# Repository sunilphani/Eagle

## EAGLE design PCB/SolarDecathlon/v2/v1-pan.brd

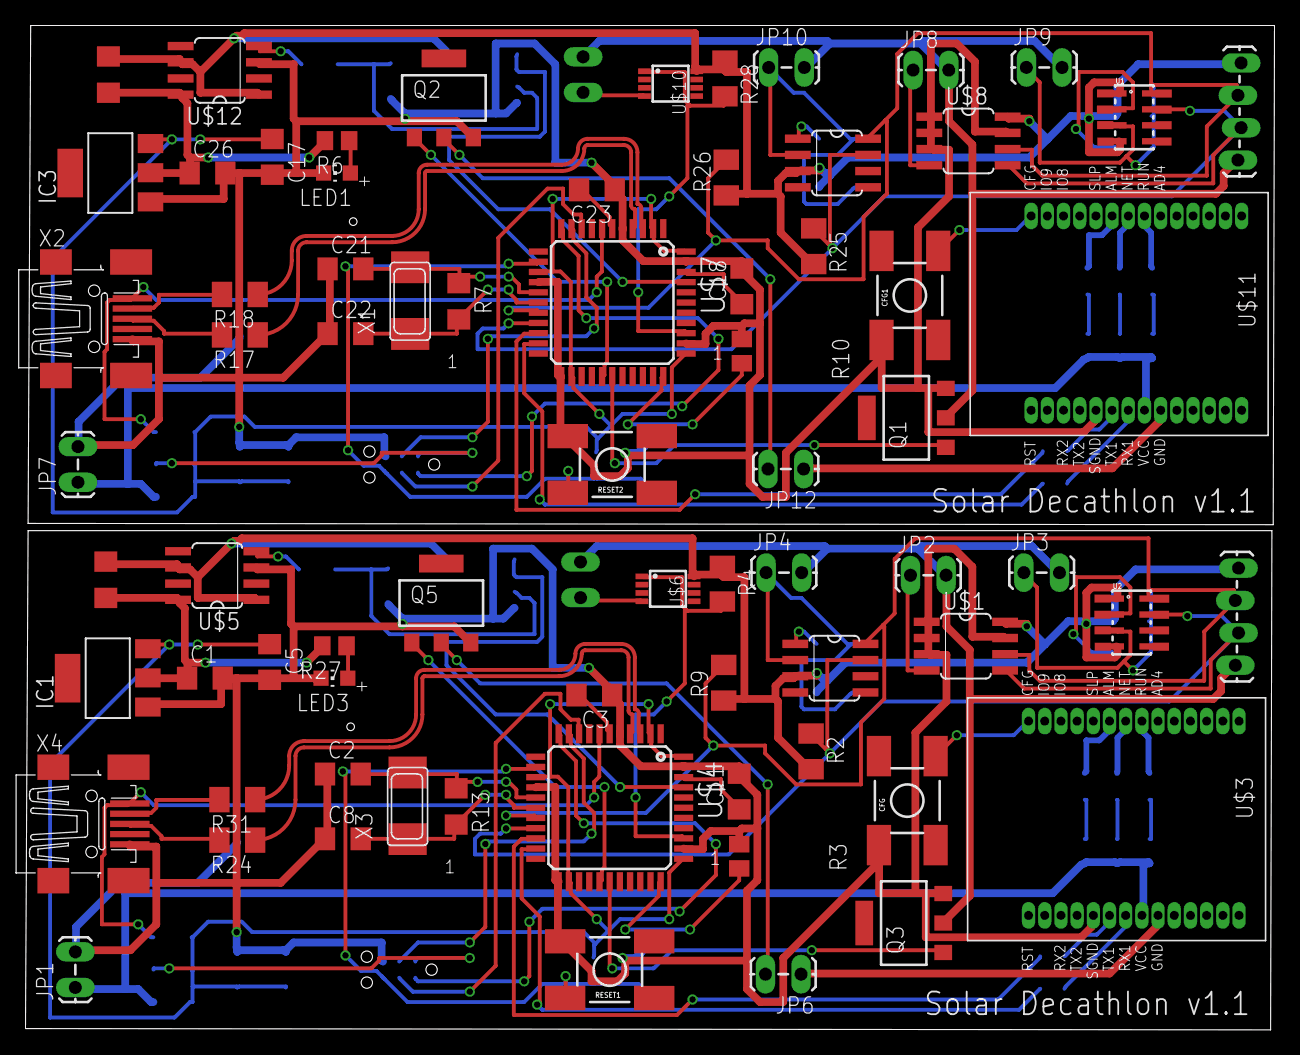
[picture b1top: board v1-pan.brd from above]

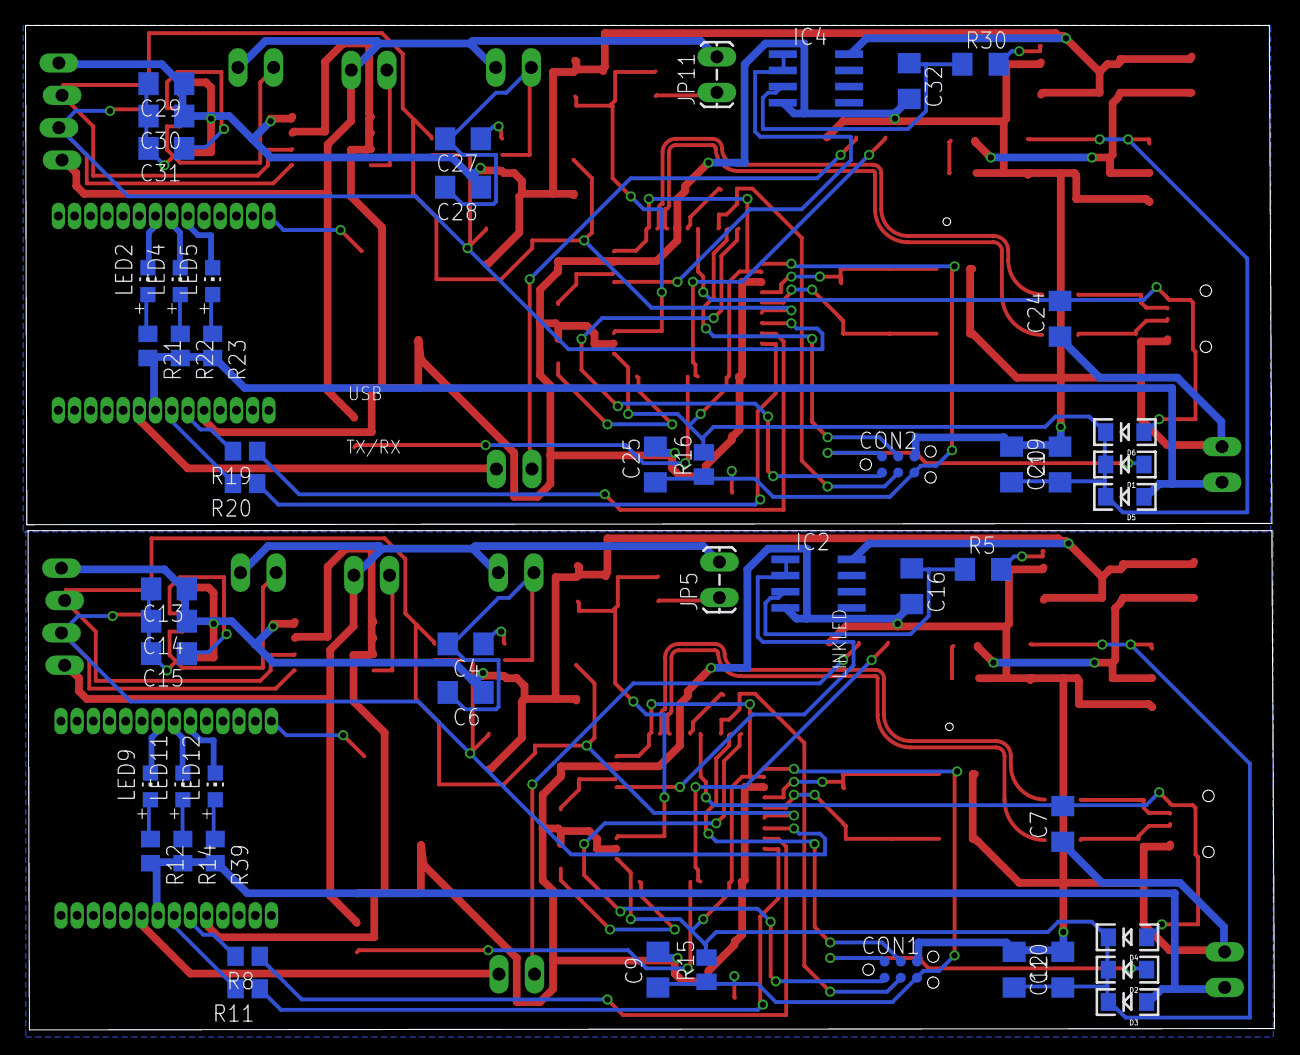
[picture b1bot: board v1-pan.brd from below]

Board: 2 copper layers, 98.0 x 78.8 mm, 124 parts (52 on the bottom side), 98 nets.

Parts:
C1, C5, C7, C10, C14, C17, C19, C24, C26, C30: 10uF; C1206
C2, C8, C21, C22: 22pF; C1206
C3, C4, C9, C11, C12, C13, C15, C18, C20, C23, C25, C27, C29, C31: 100nF; C1206
C6, C28: 220nF; C1206
C16, C32: 150nF; C1206
CFG, CFG1: Configure; TACTILE_SWITCH_SMD
CON1, CON2: SPI; TC2030-MCP-NL
D1, D2, D3, D4, D5, D6: 1N581D1206; LED-1206
IC1, IC3: REG1117; SOT223
IC2, IC4: TL072D; SO08
JP1, JP2, JP3, JP4, JP5, JP6, JP7, JP8, JP9, JP10, JP11, JP12: 1X02_LOCK_LONGPADS
JP13, JP14: 1X04_LOCK_LONGPADS
LED1, LED2, LED3, LED4, LED5, LED9, LED11, LED12: RED; CHIP-LED0805
Q1, Q2, Q3, Q5: BSP75; PG-SOT-223
R1, R29: 50m; R1206
R2, R9, R25, R26: 10k; M1206
R3, R10, R15, R16: 10k; M0805
R4, R28: 4.7k; M1206
R5, R30: 10k; R1206
R6, R8, R11, R12, R14, R19, R20, R21, R22, R23, R27, R39: 1K; R0805
R7, R13: 1M; R1206
R17, R18, R24, R31: 22; M1206
RESET1, RESET2: Reset uC; TACTILE_SWITCH_SMD
U1, U2: MPL3115A2LGA8; LGA8
U$1, U$8: M24512; SO8
U$2, U$9: CHIPCAP
U$3, U$11: SZ05-ZIGBEETHROUGHHOLE; SZ05-ZIGBEE4
U$4, U$7: ATMEGA32U4-AU; TQFP44
U$5, U$12: MAX4376F; SO8
U$6, U$10: DS1820; µSOP8
X1, X3: 16MHz; NX6035
X2, X4: MINI-USB; 32005-201

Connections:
3.3IN: C1.1, IC1.2, R1.1, R27.2, U$5.8
3.3IN1: C26.1, IC3.2, R6.2, R29.1, U$12.8
3.3V: C6.1, C13.1, C14.1, IC2.8, JP13.1, R1.2, R2.2, R4.1, R9.1, U2.1, U2.4, U$1.8, U$2.3, U$5.1, U$5.6, U$6.8
3.3V1: C28.1, C29.1, C30.1, IC4.8, JP14.1, R25.2, R26.1, R28.1, R29.2, U1.1, U1.4, U$8.8, U$9.3, U$10.8, U$12.1, U$12.6
$1: C13.2, C14.2, C15.2, JP3.1, U2.3
$2: C4.2, C6.2, JP4.1, U$2.2
$3: JP5.1, U$6.4
$4: JP8.1, U$8.4
$5: JP11.1, U$10.4
$6: C29.2, C30.2, C31.2, JP9.1, U1.3
$7: C27.2, C28.2, JP10.1, U$9.2
$12: JP2.1, U$1.4
+5V: D3.A, JP1.1, R12.2, R14.2, R39.2, U$3.VCC
+5V1: D5.A, JP7.1, R21.2, R22.2, R23.2, U$11.VCC
A0: R4.2, U$4.36, U$6.1
A5: IC2.1, IC2.2, U$4.41
A9: IC4.1, IC4.2, U$7.41
A11: R28.2, U$7.36, U$10.1
AREF: C11.1, U$4.42
AREF1: C18.1, U$7.42
D6*: Q5.1, U$4.27
D6*1: Q2.1, U$7.27
D8*: Q3.1, U$4.28
D8*1: Q1.1, U$7.28
D+USB: R24.2, X4.3
D+USB1: R17.2, X2.3
D-USB: R31.2, X4.2
D-USB1: R18.2, X2.2
GND: C1.2, C2.1, C3.1, C5.2, C7.1, C8.1, C9.2, C10.2, C11.2, C12.1, C16.2, CFG.1, CON1.GND, IC1.1, IC2.4, JP1.2, LED3.C, Q3.3, Q5.3, R3.1, RESET1.4, U$1.1, U$1.2, U$1.3, U$1.7, U$3.SND, U$4.5, U$4.15, U$4.23, U$4.35, U$4.43, U$5.3, X4.5
GND1: LED9.C, U$3.RUN
GND2: LED11.C, U$3.NET
GND3: LED12.C, U$3.ALM
GND4: C17.2, C18.2, C19.2, C20.1, C21.1, C22.1, C23.1, C24.1, C25.2, C26.2, C32.2, CFG1.1, CON2.GND, IC3.1, IC4.4, JP7.2, LED1.C, Q1.3, Q2.3, R10.1, RESET2.4, U$7.5, U$7.15, U$7.23, U$7.35, U$7.43, U$8.1, U$8.2, U$8.3, U$8.7, U$11.SND, U$12.3, X2.5
GND5: LED2.C, U$11.RUN
GND6: LED4.C, U$11.NET
GND7: LED5.C, U$11.ALM
GND_CONTROLLED: JP2.2, JP3.2, JP4.2, JP5.2, JP13.4, Q3.2
GND_CONTROLLED1: JP8.2, JP9.2, JP10.2, JP11.2, JP14.4, Q1.2
HWB: R3.2, U$4.33
HWB1: R10.2, U$7.33
ISP+5V: CON1.5V, D2.A
ISP+5V1: CON2.5V, D1.A
MISO: CON1.MISO, U$4.11
MISO1: CON2.MISO, U$7.11
MOSI: CON1.MOSI, U$4.10
MOSI1: CON2.MOSI, U$7.10
unnamed: R5.2, U$5.4
unnamed: JP6.2, Q5.2
unnamed: C16.1, IC2.3, R5.1
unnamed: C22.2, R7.2, U$7.17, X1.P$2
unnamed: LED1.A, R6.1
unnamed: C4.1, U$2.1
unnamed: C23.2, U$7.6
unnamed: JP6.1, U$3.GND
unnamed: R20.2, U$11.RX1
unnamed: R19.2, U$11.TX1
unnamed: R11.2, U$3.RX1
unnamed: LED2.A, R21.1
unnamed: C15.1, U2.2
unnamed: LED4.A, R22.1
unnamed: LED5.A, R23.1
unnamed: C3.2, U$4.6
unnamed: CFG1.4, U$11.CFG
unnamed: C27.1, U$9.1
unnamed: C31.1, U1.2
unnamed: LED3.A, R27.1
unnamed: JP12.1, U$11.GND
unnamed: JP12.2, Q2.2
unnamed: R30.2, U$12.4
unnamed: R8.2, U$3.TX1
unnamed: LED9.A, R12.1
unnamed: LED11.A, R14.1
unnamed: LED12.A, R39.1
unnamed: C32.1, IC4.3, R30.1
unnamed: CFG.4, U$3.CFG
unnamed: C8.2, R13.2, U$4.17, X3.P$2
RD_N: R31.1, U$4.3
RD_N1: R18.1, U$7.3
RD_P: R24.1, U$4.4
RD_P1: R17.1, U$7.4
RESET: C9.1, CON1.RESET, R15.1, RESET1.2, U$4.13
RESET1: C25.1, CON2.RESET, R16.1, RESET2.2, U$7.13
RX: R8.1, U$4.20
RX1: R19.1, U$7.20
SCK: CON1.SCK, U$4.9
SCK1: CON2.SCK, U$7.9
SCL: JP13.2, R9.2, U2.8, U$1.6, U$2.8, U$4.18
SCL1: JP14.2, R26.2, U1.8, U$7.18, U$8.6, U$9.8
SDA: JP13.3, R2.1, U2.7, U$1.5, U$2.7, U$4.19
SDA1: JP14.3, R25.1, U1.7, U$7.19, U$8.5, U$9.7
TX: R11.1, U$4.21
TX1: R20.1, U$7.21
VCC: C5.1, C10.1, C12.2, D2.C, D3.C, D4.C, IC1.3, R15.2, U$4.2, U$4.14, U$4.24, U$4.34, U$4.44
VCC1: C17.1, C19.1, C20.2, D1.C, D5.C, D6.C, IC3.3, R16.2, U$7.2, U$7.14, U$7.24, U$7.34, U$7.44
VUSB: C7.2, D4.A, U$4.7, X4.1
VUSB1: C24.2, D6.A, U$7.7, X2.1
XTAL1: C2.2, R13.1, U$4.16, X3.P$1
XTAL2: C21.2, R7.1, U$7.16, X1.P$1

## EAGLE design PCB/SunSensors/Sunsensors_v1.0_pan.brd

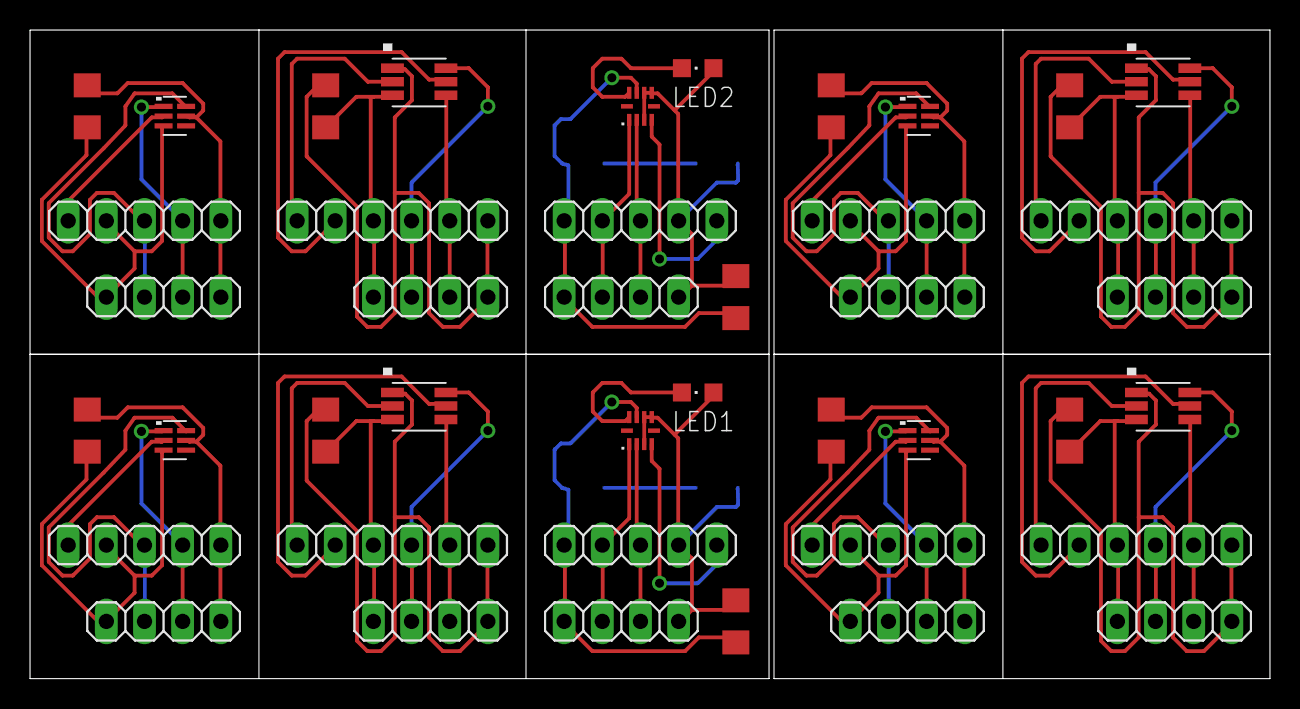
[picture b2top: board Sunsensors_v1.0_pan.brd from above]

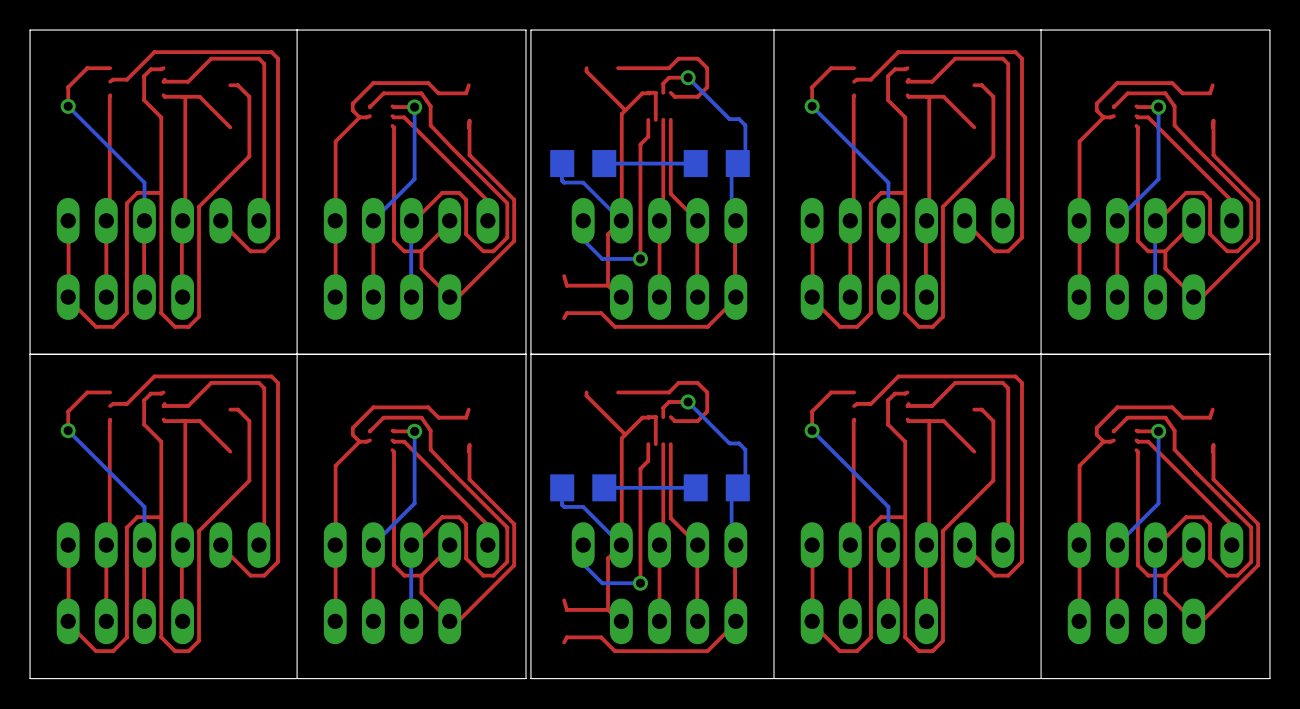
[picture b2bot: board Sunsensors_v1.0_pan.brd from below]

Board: 2 copper layers, 82.5 x 43.2 mm, 46 parts (4 on the bottom side), 46 nets.

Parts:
C1, C2, C3, C5, C6, C7, C9, C10, C11, C12: 0.1uF; C1206
C4, C8: 15uF; C1206
IC1, IC2: SI1145; QFN-10
JP1, JP3, JP5, JP7, JP9, JP11, JP13, JP15, JP17, JP19: 1X04
JP2, JP6, JP8, JP12, JP14, JP18: 1X05
JP4, JP10, JP16, JP20: 1X06
LED1, LED2: CHIPLED_0805
R1, R2: 30; C1206
U$1, U$3, U$5, U$8: TSL25911FN; ODFN6
U$2, U$4, U$6, U$9: TSL2561T; TMB-6

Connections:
ADDR1: JP4.6, U$9.P$2
ADDR2: JP10.6, U$2.P$2
ADDR3: JP16.6, U$4.P$2
ADDR4: JP20.6, U$6.P$2
GND: C3.2, C4.2, IC1.8, JP5.4, JP6.5
GND1: C2.2, JP1.4, JP2.4, U$8.P$3
GND2: C1.2, JP3.4, JP4.4, U$9.P$3
GND3: C7.2, C8.2, IC2.8, JP11.4, JP12.5
GND4: C6.2, JP7.4, JP8.4, U$1.P$3
GND5: C5.2, JP9.4, JP10.4, U$2.P$3
GND6: C10.2, JP13.4, JP14.4, U$3.P$3
GND7: C9.2, JP15.4, JP16.4, U$4.P$3
GND8: C12.2, JP17.4, JP18.4, U$5.P$3
GND9: C11.2, JP19.4, JP20.4, U$6.P$3
INT1: JP4.5, U$9.P$5
INT2: JP2.5, U$8.P$2
INT3: IC1.4, JP6.1
INT4: JP10.5, U$2.P$5
INT5: JP8.5, U$1.P$2
INT6: IC2.4, JP12.1
INT7: JP16.5, U$4.P$5
INT8: JP14.5, U$3.P$2
INT9: JP20.5, U$6.P$5
INT10: JP18.5, U$5.P$2
unnamed: C4.1, R1.1
unnamed: IC2.9, LED2.C
unnamed: IC1.9, LED1.C
unnamed: C8.1, R2.1
SCL: IC1.2, JP1.2, JP2.2, JP3.2, JP4.2, JP5.2, JP6.3, U$8.P$1, U$9.P$4
SCL1: IC2.2, JP7.2, JP8.2, JP9.2, JP10.2, JP11.2, JP12.3, U$1.P$1, U$2.P$4
SCL2: JP13.2, JP14.2, JP15.2, JP16.2, U$3.P$1, U$4.P$4
SCL3: JP17.2, JP18.2, JP19.2, JP20.2, U$5.P$1, U$6.P$4
SDA: IC1.1, JP1.3, JP2.3, JP3.3, JP4.3, JP5.3, JP6.4, U$8.P$6, U$9.P$6
SDA1: IC2.1, JP7.3, JP8.3, JP9.3, JP10.3, JP11.3, JP12.4, U$1.P$6, U$2.P$6
SDA2: JP13.3, JP14.3, JP15.3, JP16.3, U$3.P$6, U$4.P$6
SDA3: JP17.3, JP18.3, JP19.3, JP20.3, U$5.P$6, U$6.P$6
VCC: C3.1, IC1.3, IC1.6, IC1.7, JP5.1, JP6.2, LED1.A, R1.2
VCC1: C2.1, JP1.1, JP2.1, U$8.P$5
VCC2: C1.1, JP3.1, JP4.1, U$9.P$1
VCC3: C7.1, IC2.3, IC2.6, IC2.7, JP11.1, JP12.2, LED2.A, R2.2
VCC4: C6.1, JP7.1, JP8.1, U$1.P$5
VCC5: C5.1, JP9.1, JP10.1, U$2.P$1
VCC6: C10.1, JP13.1, JP14.1, U$3.P$5
VCC7: C9.1, JP15.1, JP16.1, U$4.P$1
VCC8: C12.1, JP17.1, JP18.1, U$5.P$5
VCC9: C11.1, JP19.1, JP20.1, U$6.P$1

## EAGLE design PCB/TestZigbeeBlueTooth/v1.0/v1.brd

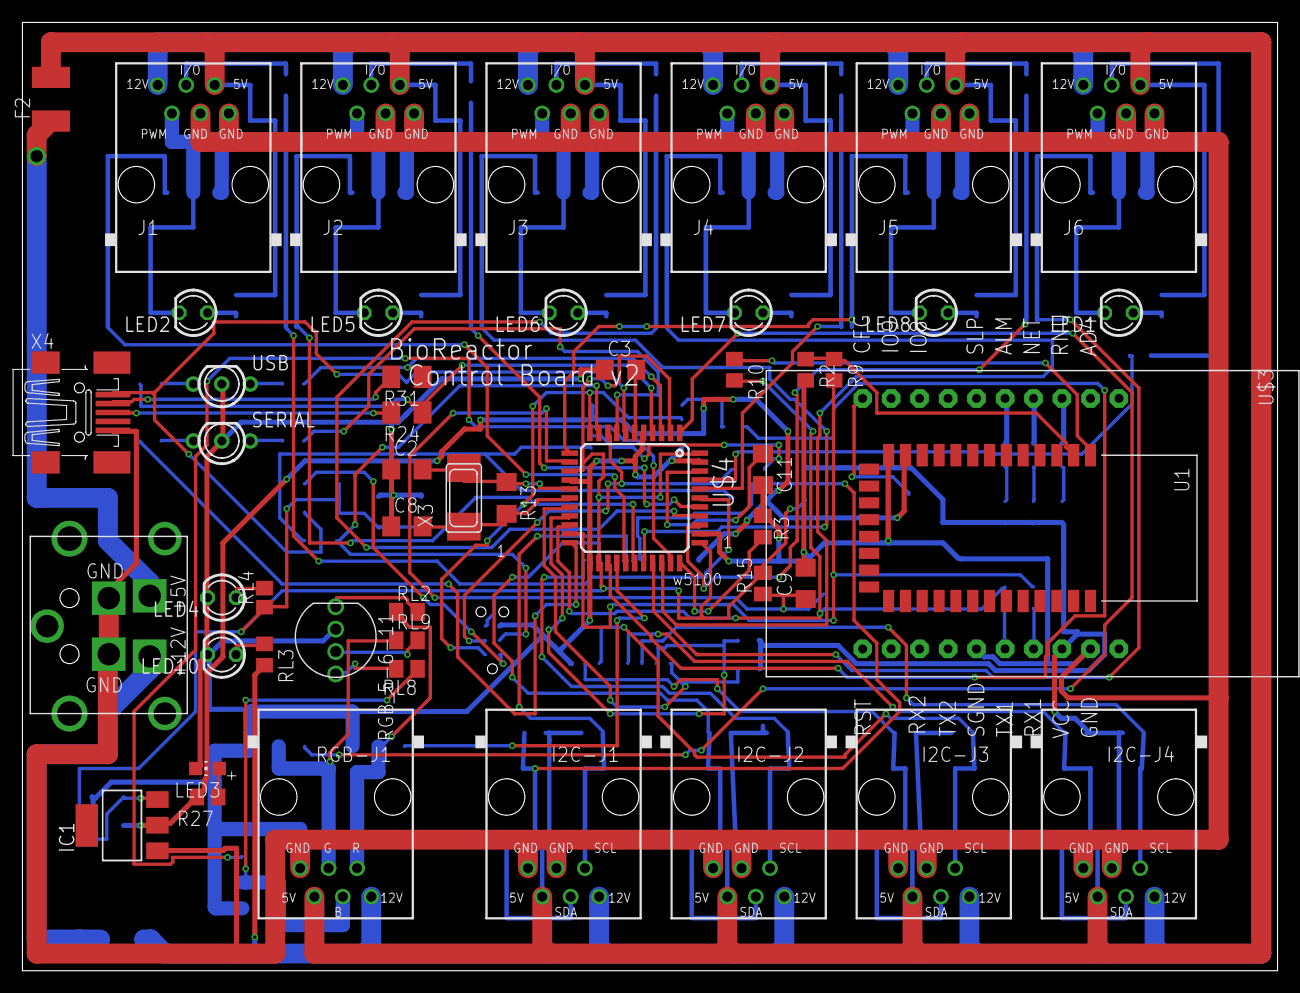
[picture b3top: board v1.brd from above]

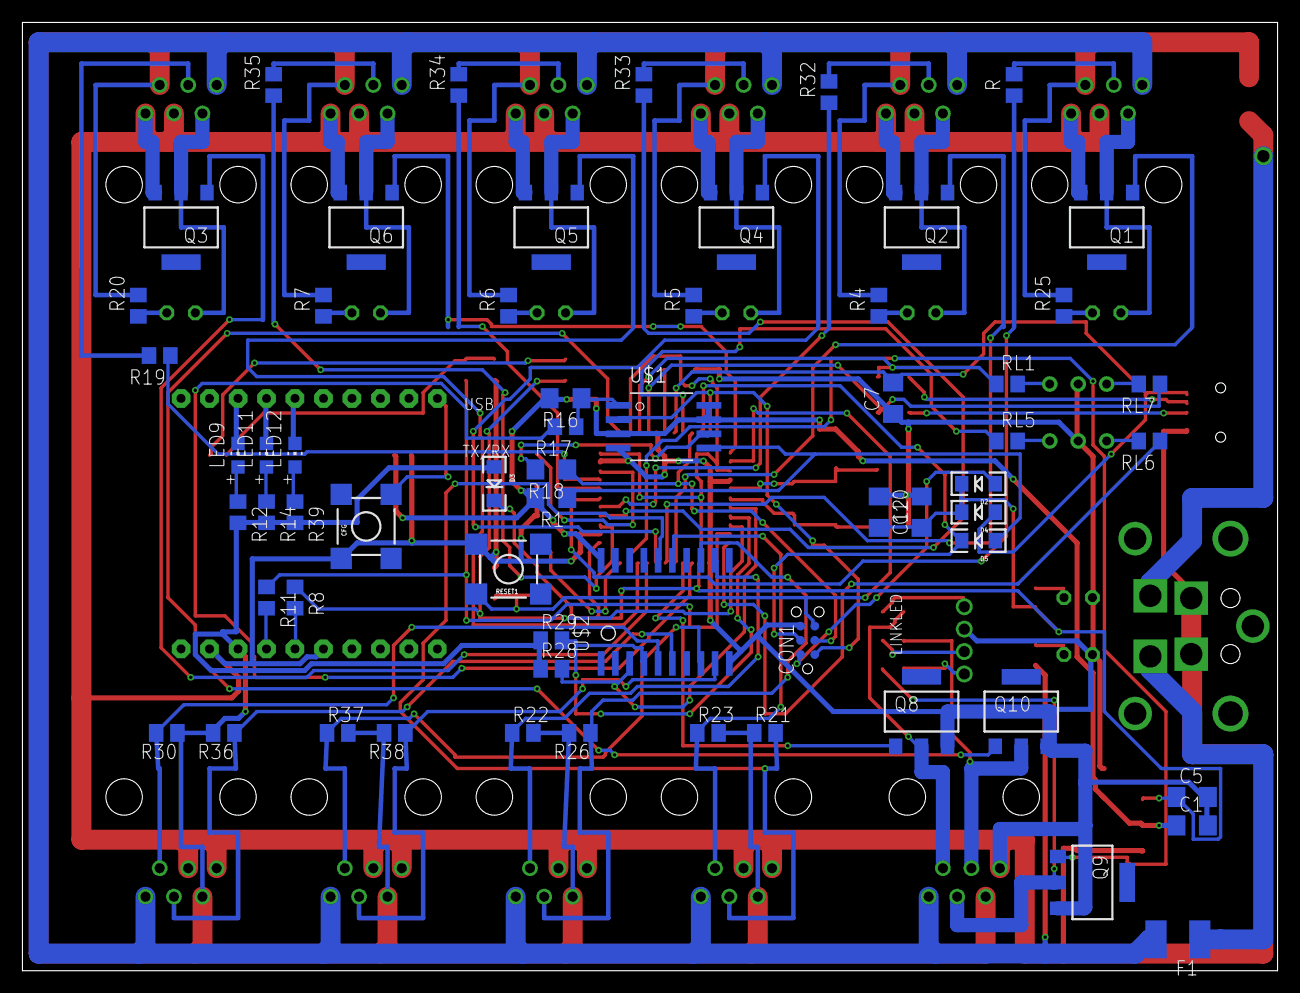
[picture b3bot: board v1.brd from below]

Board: 2 copper layers, 111.9 x 84.6 mm, 112 parts (62 on the bottom side), 97 nets.

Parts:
C1, C5, C7, C10: 10uF; C1206
C2, C8: 22pF; C1206
C3, C9, C11, C12: 100nF; C1206
CFG: Configure; TACTILE_SWITCH_SMD
CON1: SPI; TC2030-MCP-NL
D2, D3, D4, D5: 1N581D1206; LED-1206
F1, F2: 0.5A; C1812
I2C-J1, I2C-J2, I2C-J3, I2C-J4: RJ12STRAIGHT-I2C; RJ12-STRAIGHT-I2C
IC1: REG1117; SOT223
J1, J2, J3, J4, J5, J6: RJ12; RJ12-STRAIGHT
LED1, LED2, LED5, LED6, LED8: Blue; LED3MM
LED3, LED9, LED11, LED12: RED; CHIP-LED0805
LED4, LED10: RED; LED3MM
LED7: BLue; LED3MM
Q1, Q2, Q3, Q4, Q5, Q6, Q8, Q9, Q10: BSP75; PG-SOT-223
R, R4, R5, R6, R7, R17, R19, R20, R25, R32, R33, R34, R35: 1k; R0805
R1, R16, R18: 10k; R1206
R2: 2.2K; R0805
R3, R15: 10k; M0805
R8, R10, R11, R12, R14, R27, R39: 1K; R0805
R9: 1.2K; R0805
R13: 1M; R1206
R21, R22, R23, R26, R28, R29, R30, R36, R37, R38: 10K; M0805
R24, R31: 22; M1206
RESET1: Reset uC; TACTILE_SWITCH_SMD
RGB-J1: RJ12; RJ12-STRAIGHT-RGB
RGB_5-6-11: LED-TRICOLOR-THROUGHHOLE
RL1, RL3, RL4, RL5, RL6, RL7: 1K; R0805
RL2, RL8, RL9: 1K; M0805
SERIAL: BICOLOR-LED; BICOLOR-3MM
U1: HC_05; BLUETOOTH_SMD
U$1: SST25VF064C; SOIC_8-LEAD
U$2: PCA9518; SO20W
U$3: SZ05-ZIGBEE
U$4: ATMEGA32U4-AU; TQFP44
U$6: KPJX-4S-S
USB: BICOLOR-LED COMMON CAT; BICOLOR-3MM
X3: 16MHz; NX6035
X4: MINI-USB; 32005-201

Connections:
3.3V: C1.1, IC1.2, R1.2, R16.2, R27.2, U1.12, U$1.RST/HOLD, U$1.VDD, U$1.WP, U$2.20
+5V: D3.A, F2.2, I2C-J1.+5V, I2C-J2.+5V, I2C-J3.+5V, I2C-J4.+5V, J1.+5V, J2.+5V, J3.+5V, J4.+5V, J5.+5V, J6.+5V, R4.2, R5.2, R6.2, R7.2, R12.2, R14.2, R20.2, R21.1, R22.2, R23.2, R25.2, R26.2, R28.1, R29.1, R30.1, R36.2, R37.2, R38.2, R39.2, RGB-J1.+5V, U$3.VCC
+5V/1: C5.1, C10.1, C12.2, D2.C, D3.C, D4.C, IC1.3, R15.2, RL4.1, U$4.2, U$4.14, U$4.24, U$4.34, U$4.44
+12V: F1.2, I2C-J1.+12V, I2C-J2.+12V, I2C-J3.+12V, I2C-J4.+12V, J1.+12V, J2.+12V, J3.+12V, J4.+12V, J5.+12V, J6.+12V, RGB-J1.+12V, RL3.2
A0: R35.1, U$4.36
A1: R33.1, U$4.37
A2: R32.1, U$4.38
A3: R.1, U$4.39
A4: R34.1, U$4.40
A5: R19.1, U$4.41
AREF: C11.1, U$4.42
CS: R17.2, U$4.25
D2B5: R2.1, R9.1, U1.2
D5*: Q5.1, U$4.31
D6*: Q1.1, U$4.27
D7*: Q10.1, U$4.1
D8*: Q2.1, U$4.28
D9*: Q4.1, U$4.29
D10*: Q3.1, U$4.30
D11*: Q6.1, U$4.12
D12*: Q8.1, U$4.26
D13*: Q9.1, U$4.32
D+USB: R24.2, X4.3
D-USB: R31.2, X4.2
FMOSI: D5.A, R1.1, U$1.SI
GND: C1.2, C2.1, C3.1, C5.2, C7.1, C8.1, C9.2, C10.2, C11.2, C12.1, CFG.1, CON1.GND, I2C-J1.GND1, I2C-J1.GND2, I2C-J2.GND1, I2C-J2.GND2, I2C-J3.GND1, I2C-J3.GND2, I2C-J4.GND1, I2C-J4.GND2, IC1.1, J1.GND1, J1.GND2, J2.GND1, J2.GND2, J3.GND1, J3.GND2, J4.GND1, J4.GND2, J5.GND1, J5.GND2, J6.GND1, J6.GND2, LED3.C, LED4.K, LED10.K, Q1.3, Q2.3, Q3.3, Q4.3, Q5.3, Q6.3, Q8.3, Q9.3, Q10.3, R2.2, R3.1, RESET1.4, RGB-J1.GND1, RGB_5-6-11.GND, SERIAL.2, U1.13, U$1.VSS, U$2.10, U$3.GND, U$3.SGND, U$4.5, U$4.15, U$4.23, U$4.35, U$4.43, U$6.GND1, U$6.GND2, USB.2, X4.5
GND1: LED9.C, U$3.RNU
GND2: LED11.C, U$3.NET
GND3: LED12.C, U$3.ALM
HWB: R3.2, U$4.33
ISP+5V: CON1.5V, D2.A
MISO: CON1.MISO, U$1.SO, U$4.11
MOSI: CON1.MOSI, D5.C, U$4.10
unnamed: J3.PWM, LED6.K, Q4.2
unnamed: J2.I/O, R32.2
unnamed: J6.I/O, R19.2
unnamed: LED5.A, R4.1
unnamed: J4.PWM, LED7.K, Q5.2
unnamed: Q10.2, RGB-J1.G, RL9.1
unnamed: J3.I/O, R33.2
unnamed: RL1.2, USB.3
unnamed: LED1.A, R20.1
unnamed: R16.1, R17.1, U$1.CE
unnamed: R11.2, U$3.RX1
unnamed: LED4.A, RL4.2
unnamed: RL5.2, SERIAL.3
unnamed: RL7.2, USB.1
unnamed: RL6.2, SERIAL.1
unnamed: C3.2, U$4.6
unnamed: LED2.A, R25.1
unnamed: J1.I/O, R.2
unnamed: J5.PWM, LED8.K, Q6.2
unnamed: LED3.A, R27.1
unnamed: J6.PWM, LED1.K, Q3.2
unnamed: LED6.A, R5.1
unnamed: R18.2, U$1.SCK
unnamed: R8.2, U$3.TX1
unnamed: LED9.A, R12.1
unnamed: LED11.A, R14.1
unnamed: LED12.A, R39.1
unnamed: J2.PWM, LED5.K, Q2.2
unnamed: J4.I/O, R34.2
unnamed: LED7.A, R6.1
unnamed: J5.I/O, R35.2
unnamed: LED8.A, R7.1
unnamed: J1.PWM, LED2.K, Q1.2
unnamed: CFG.4, U$3.CFG
unnamed: RGB_5-6-11.RED, RL2.2
unnamed: RGB_5-6-11.BLU, RL8.2
unnamed: F2.1, U$6.+5V
unnamed: F1.1, U$6.+12V
unnamed: RGB_5-6-11.GRN, RL9.2
unnamed: C8.2, R13.2, U$4.17, X3.P$2
unnamed: Q9.2, RGB-J1.B, RL8.1
unnamed: Q8.2, RGB-J1.R, RL2.1
unnamed: R10.1, U1.1
unnamed: LED10.A, RL3.1
RD+: R24.1, RL7.1, U$4.4
RD-: R31.1, RL1.1, U$4.3
RESET: C9.1, CON1.RESET, R15.1, RESET1.2, U$4.13
RX: R8.1, R10.2, U$4.20
RXLED: RL5.1, U$4.8
SCK: CON1.SCK, R18.1, U$4.9
SCL: R28.2, U$2.3, U$4.18
SCL1: I2C-J4.SCL, R30.2, U$2.5
SCL2: I2C-J3.SCL, R37.1, U$2.8
SCL3: I2C-J2.SCL, R22.1, U$2.12
SCL4: I2C-J1.SCL, R23.1, U$2.15
SDA: R29.2, U$2.4, U$4.19
SDA1: I2C-J4.SDA, R36.1, U$2.6
SDA2: I2C-J3.SDA, R38.1, U$2.9
SDA3: I2C-J2.SDA, R26.1, U$2.13
SDA4: I2C-J1.SDA, R21.2, U$2.16
TX: R9.2, R11.1, U$4.21
TXLED: RL6.1, U$4.22
VUSB: C7.2, D4.A, U$4.7, X4.1
XTAL1: C2.2, R13.1, U$4.16, X3.P$1

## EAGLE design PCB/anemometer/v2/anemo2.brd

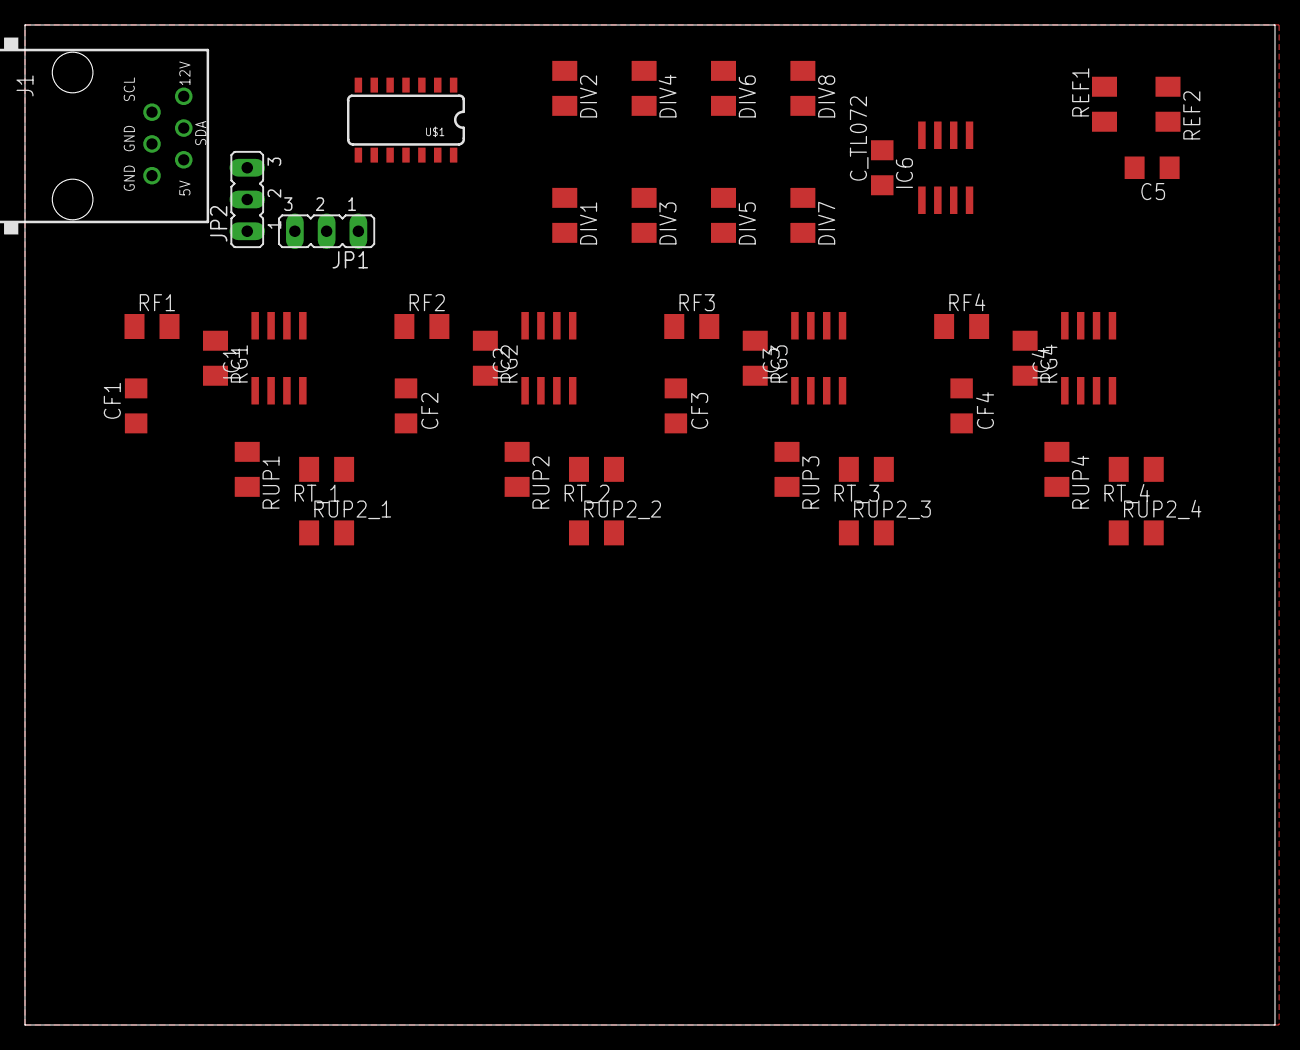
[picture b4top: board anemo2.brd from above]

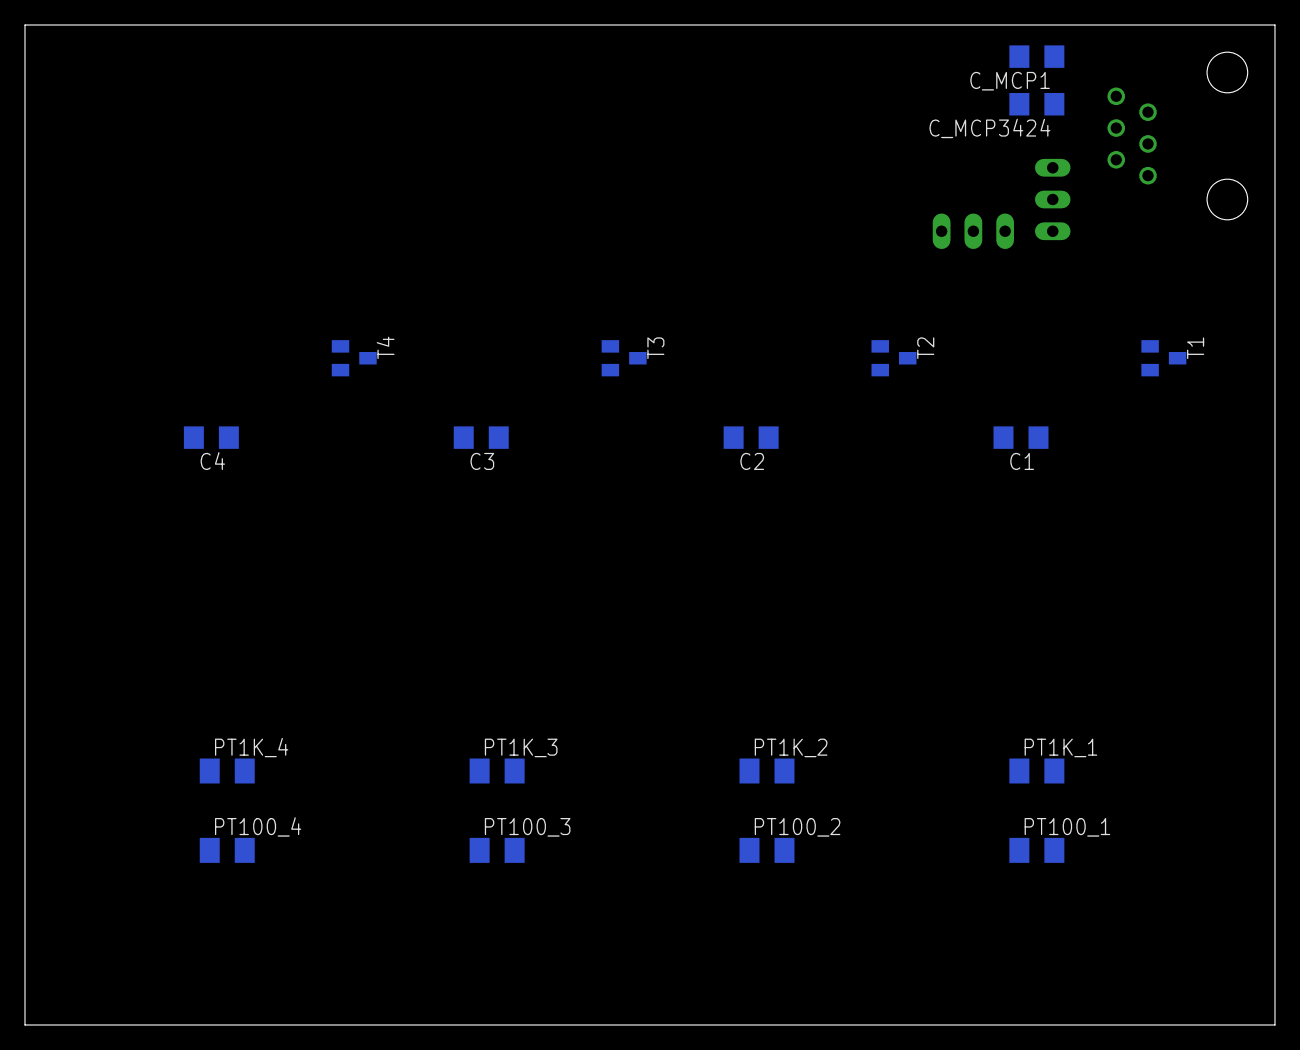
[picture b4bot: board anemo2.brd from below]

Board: 2 copper layers, 100.0 x 80.0 mm, 63 parts (18 on the bottom side), 45 nets, no tracks yet.

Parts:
C1, C2, C3, C4, C5: 100n; C1206
CF1, CF2, CF3, CF4: 330n; C1206
C_MCP1: 10µ; C1206
C_MCP3424: 100n; C1206
C_TL072: 100n; C1206
DIV1, DIV3, DIV5, DIV7: 20k; M1206
DIV2, DIV4, DIV6, DIV8: 10k; M1206
IC1, IC2, IC3, IC4: AD620R; SO8
IC6: TL072D; SO08
J1: RJ12STRAIGHT-I2C; RJ12-STRAIGHT-I2C
JP1, JP2: JP2
PT1K_1, PT1K_2, PT1K_3, PT1K_4, PT100_1, PT100_2, PT100_3, PT100_4: 90.9; M1206
REF1, REF2: 100k; M1206
RF1, RF2, RF3, RF4: 100; M1206
RG1, RG2, RG3, RG4: 500; M1206
RT_1, RT_2, RT_3, RT_4: 90.9; M1206
RUP1, RUP2, RUP3, RUP4: 10; M1206
RUP2_1, RUP2_2, RUP2_3, RUP2_4: 100; M1206
T1, T2, T3, T4: BC846; SOT23
U$1: MCP3424(SO14); 14LDSOIC

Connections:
5V: C_MCP1.2, C_MCP3424.2, J1.+5V, JP1.1, JP2.1, U$1.6
ADR0: JP2.2, U$1.9
ADR1: JP1.2, U$1.10
GND: C1.2, C2.2, C3.2, C4.2, C5.2, CF1.1, CF2.1, CF3.1, CF4.1, C_MCP1.1, C_MCP3424.1, C_TL072.1, DIV2.1, DIV4.1, DIV6.1, DIV8.1, IC1.4, IC2.4, IC3.4, IC4.4, IC6.4, J1.GND1, J1.GND2, JP1.3, JP2.3, PT1K_1.1, PT1K_2.1, PT1K_3.1, PT1K_4.1, PT100_1.1, PT100_2.1, PT100_3.1, PT100_4.1, REF2.1, U$1.2, U$1.4, U$1.5, U$1.12, U$1.14
IN+1: IC1.3, RT_1.2, RUP2_1.1
IN+2: IC2.3, RT_2.2, RUP2_2.1
IN+3: IC3.3, RT_3.2, RUP2_3.1
IN+4: IC4.3, RT_4.2, RUP2_4.1
IN-1: IC1.2, PT100_1.2, RUP1.1
IN-2: IC2.2, PT100_2.2, RUP2.1
IN-3: IC3.2, PT100_3.2, RUP3.1
IN-4: IC4.2, PT100_4.2, RUP4.1
unnamed: IC1.1, RG1.2
unnamed: IC1.8, RG1.1
unnamed: IC2.8, RG2.1
unnamed: IC2.1, RG2.2
unnamed: IC3.1, RG3.2
unnamed: IC3.8, RG3.1
unnamed: IC4.1, RG4.2
unnamed: IC4.8, RG4.1
unnamed: RUP1.2, RUP2_1.2, T1.2
unnamed: C5.1, IC6.3, REF1.1, REF2.2
unnamed: RUP2.2, RUP2_2.2, T2.2
unnamed: RUP2_3.2, RUP3.2, T3.2
unnamed: RUP2_4.2, RUP4.2, T4.2
unnamed: IC1.6, RF1.2
unnamed: IC2.6, RF2.2
unnamed: IC3.6, RF3.2
unnamed: IC4.6, RF4.2
unnamed: PT1K_1.2, RT_1.1
unnamed: PT1K_2.2, RT_2.1
unnamed: PT1K_3.2, RT_3.1
unnamed: PT1K_4.2, RT_4.1
OUT1: CF1.2, DIV1.2, RF1.1, T1.1
OUT2: CF2.2, DIV3.2, RF2.1, T2.1
OUT3: CF3.2, DIV5.2, RF3.1, T3.1
OUT4: CF4.2, DIV7.2, RF4.1, T4.1
REF: IC1.5, IC2.5, IC3.5, IC4.5, IC6.1, IC6.2
SCL: J1.SCL, U$1.8
SDA: J1.SDA, U$1.7
SIG1: DIV1.1, DIV2.2, U$1.1
SIG2: DIV3.1, DIV4.2, U$1.3
SIG3: DIV5.1, DIV6.2, U$1.11
SIG4: DIV7.1, DIV8.2, U$1.13
VCC: C1.1, C2.1, C3.1, C4.1, C_TL072.2, IC1.7, IC2.7, IC3.7, IC4.7, IC6.8, J1.+12V, REF1.2, T1.3, T2.3, T3.3, T4.3

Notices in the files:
parts and their libraries:
lpatiny: ©2009 ROFA.cz - modified and updated by Robert Darlington ‹rdarlington@gmail.com›
SparkFun: Licensing: CC v3.0 Share-Alike You are welcome to use this library for commercial purposes.
